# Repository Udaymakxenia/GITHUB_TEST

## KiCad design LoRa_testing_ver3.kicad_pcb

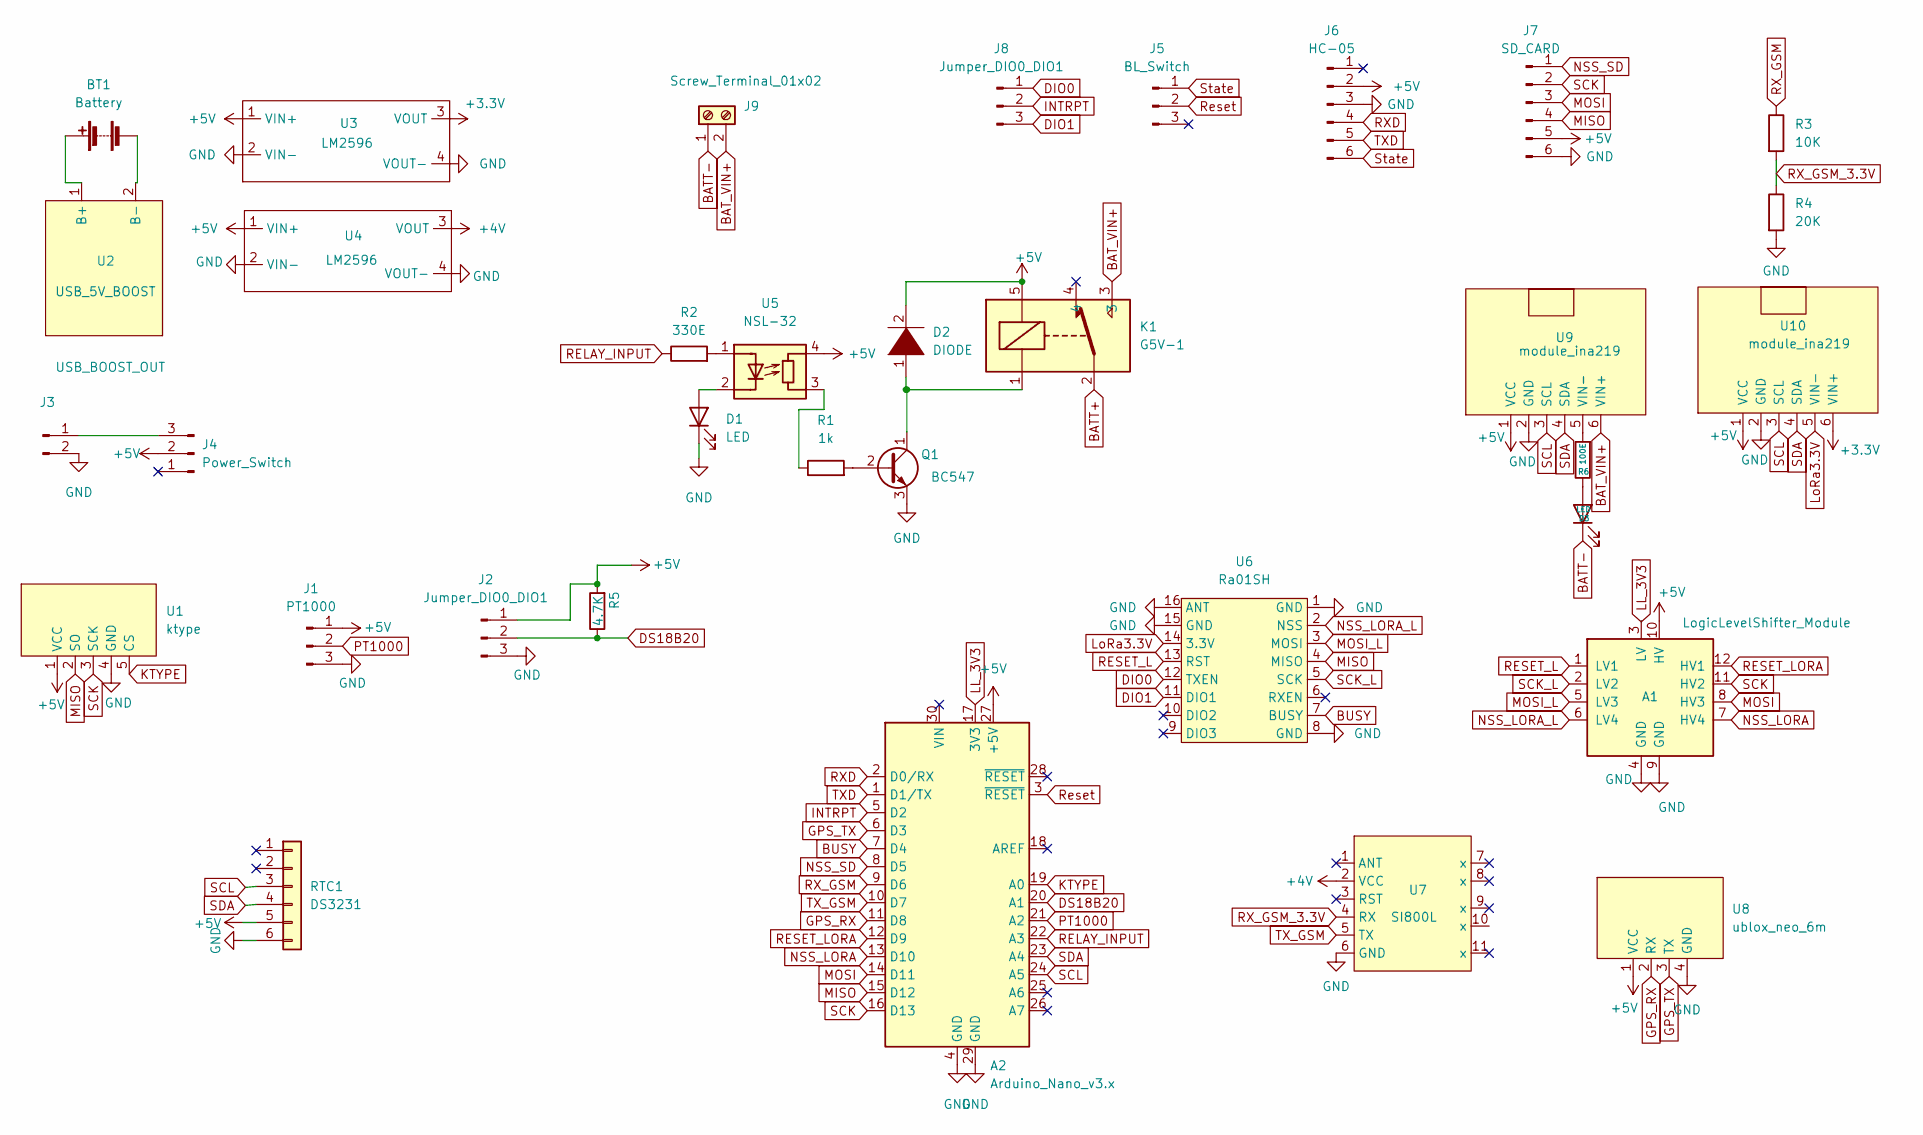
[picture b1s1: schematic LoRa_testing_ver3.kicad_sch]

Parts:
A1: LogicLevelShifter_Module; PinHeader_1x12_P2.54mm_Vertical
A2: Arduino_Nano_v3.x; Arduino_Nano
BT1: Battery; BatteryHolder_MPD_BH-18650-PC2
D1: LED; LED_D3.0mm
D2: DIODE; D_DO-41_SOD81_P3.81mm_Vertical_AnodeUp
D3: LED; LED_D5.0mm
J1: PT1000; PinHeader_1x03_P2.54mm_Vertical
J2, J8: Jumper_DIO0_DIO1; PinHeader_1x03_P2.54mm_Vertical
J3: USB_BOOST_OUT; PinHeader_1x02_P2.54mm_Vertical
J4: Power_Switch; PinHeader_1x03_P2.54mm_Vertical
J5: BL_Switch; PinHeader_1x03_P2.54mm_Vertical
J6: HC-05; PinHeader_1x06_P2.54mm_Vertical
J7: SD_CARD; PinHeader_1x06_P2.54mm_Vertical
J9: Screw_Terminal_01x02; TerminalBlock_Phoenix_MKDS-1,5-2-5.08_1x02_P5.08mm_Horizont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
K1: G5V-1; Relay_SPDT_SANYOU_SRD_Series_Form_C
Q1: BC547; TO-92_Inline
R1: 1k; R_Axial_DIN0207_L6.3mm_D2.5mm_P7.62mm_Horizontal
R2: 330E; R_Axial_DIN0411_L9.9mm_D3.6mm_P7.62mm_Vertical
R3: 10K; R_Axial_DIN0207_L6.3mm_D2.5mm_P7.62mm_Horizontal
R4: 20K; R_Axial_DIN0207_L6.3mm_D2.5mm_P7.62mm_Horizontal
R5: 4.7K; R_Axial_DIN0207_L6.3mm_D2.5mm_P7.62mm_Horizontal
R6: 100E; R_Axial_DIN0207_L6.3mm_D2.5mm_P10.16mm_Horizontal
RTC1: DS3231; PinHeader_1x06_P2.54mm_Vertical
U1: ktype; PinHeader_1x05_P2.54mm_Vertical
U2: USB_5V_BOOST; PinHeader_1x06_P2.54mm_Vertical
U3, U4: LM2596
U5: NSL-32; OPTOCOUPLER
U6: Ra01SH; LoRa Ra01sh
U7: SI800L; GSM
U8: ublox_neo_6m; PinHeader_1x04_P2.54mm_Vertical
U9, U10: module_ina219

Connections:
+3.3V: U3.3 (VOUT), U10.6 (VIN+)
+4V: U4.3 (VOUT), U7.2 (VCC)
+5V: A1.10 (HV), A2.27 (+5V), D2.2 (A), J1.1, J2.1, J4.2, J6.2, J7.5, K1.5, R5.2, RTC1.5, U1.1 (VCC), U3.1 (VIN+), U4.1 (VIN+), U5.4 (R), U8.1 (VCC), U9.1 (VCC), U10.1 (VCC)
BATT+: K1.2, K1.6
BATT-: D3.1 (K), J9.1
BAT_VIN+: J9.2, K1.3, U9.6 (VIN+)
BUSY: A2.7 (D4), U6.7 (BUSY)
DIO0: J8.1, U6.12 (TXEN)
DIO1: J8.3, U6.11 (DIO1)
DS18B20: A2.20 (A1), J2.2, R5.1
GND: A1.4 (GND), A1.9 (GND), A2.4 (GND), A2.29 (GND), D1.1 (K), J1.3, J2.3, J3.2, J6.3, J7.6, Q1.3 (E), R4.2, RTC1.6, U1.4 (GND), U3.2 (VIN-), U3.4 (VOUT-), U4.2 (VIN-), U4.4 (VOUT-), U6.1 (GND), U6.8 (GND), U6.15 (GND), U6.16 (ANT), U7.6 (GND), U8.4 (GND), U9.2 (GND), U10.2 (GND)
GPS_RX: A2.11 (D8), U8.2 (RX)
GPS_TX: A2.6 (D3), U8.3 (TX)
INTRPT: A2.5 (D2), J8.2
KTYPE: A2.19 (A0), U1.5 (CS)
LL_3V3: A1.3 (LV), A2.17 (3V3)
LoRa3.3V: U6.14 (3.3V), U10.5 (VIN-)
MISO: A2.15 (D12), J7.4, U1.2 (SO), U6.4 (MISO)
MOSI: A1.8 (HV3), A2.14 (D11), J7.3
MOSI_L: A1.5 (LV3), U6.3 (MOSI)
NSS_LORA: A1.7 (HV4), A2.13 (D10)
NSS_LORA_L: A1.6 (LV4), U6.2 (NSS)
NSS_SD: A2.8 (D5), J7.1
unnamed: BT1.1 (+), U2.1 (B+)
unnamed: BT1.2 (-), U2.2 (B-)
unnamed: D1.2 (A), U5.2 (K)
unnamed: D2.1 (K), K1.1, Q1.1 (C)
unnamed: D3.2 (A), R6.1
unnamed: J3.1, J4.3
unnamed: Q1.2 (B), R1.2
unnamed: R1.1, U5.3 (R)
unnamed: R2.2, U5.1 (A)
unnamed: R6.2, U9.5 (VIN-)
PT1000: A2.21 (A2), J1.2
RELAY_INPUT: A2.22 (A3), R2.1
RESET_L: A1.1 (LV1), U6.13 (RST)
RESET_LORA: A1.12 (HV1), A2.12 (D9)
RXD: A2.2 (D0/RX), J6.4
RX_GSM: A2.9 (D6), R3.1
RX_GSM_3.3V: R3.2, R4.1, U7.4 (RX)
Reset: A2.3 (~RESET), J5.2
SCK: A1.11 (HV2), A2.16 (D13), J7.2, U1.3 (SCK)
SCK_L: A1.2 (LV2), U6.5 (SCK)
SCL: A2.24 (A5), RTC1.3, U9.3 (SCL), U10.3 (SCL)
SDA: A2.23 (A4), RTC1.4, U9.4 (SDA), U10.4 (SDA)
State: J5.1, J6.6
TXD: A2.1 (D1/TX), J6.5
TX_GSM: A2.10 (D7), U7.5 (TX)

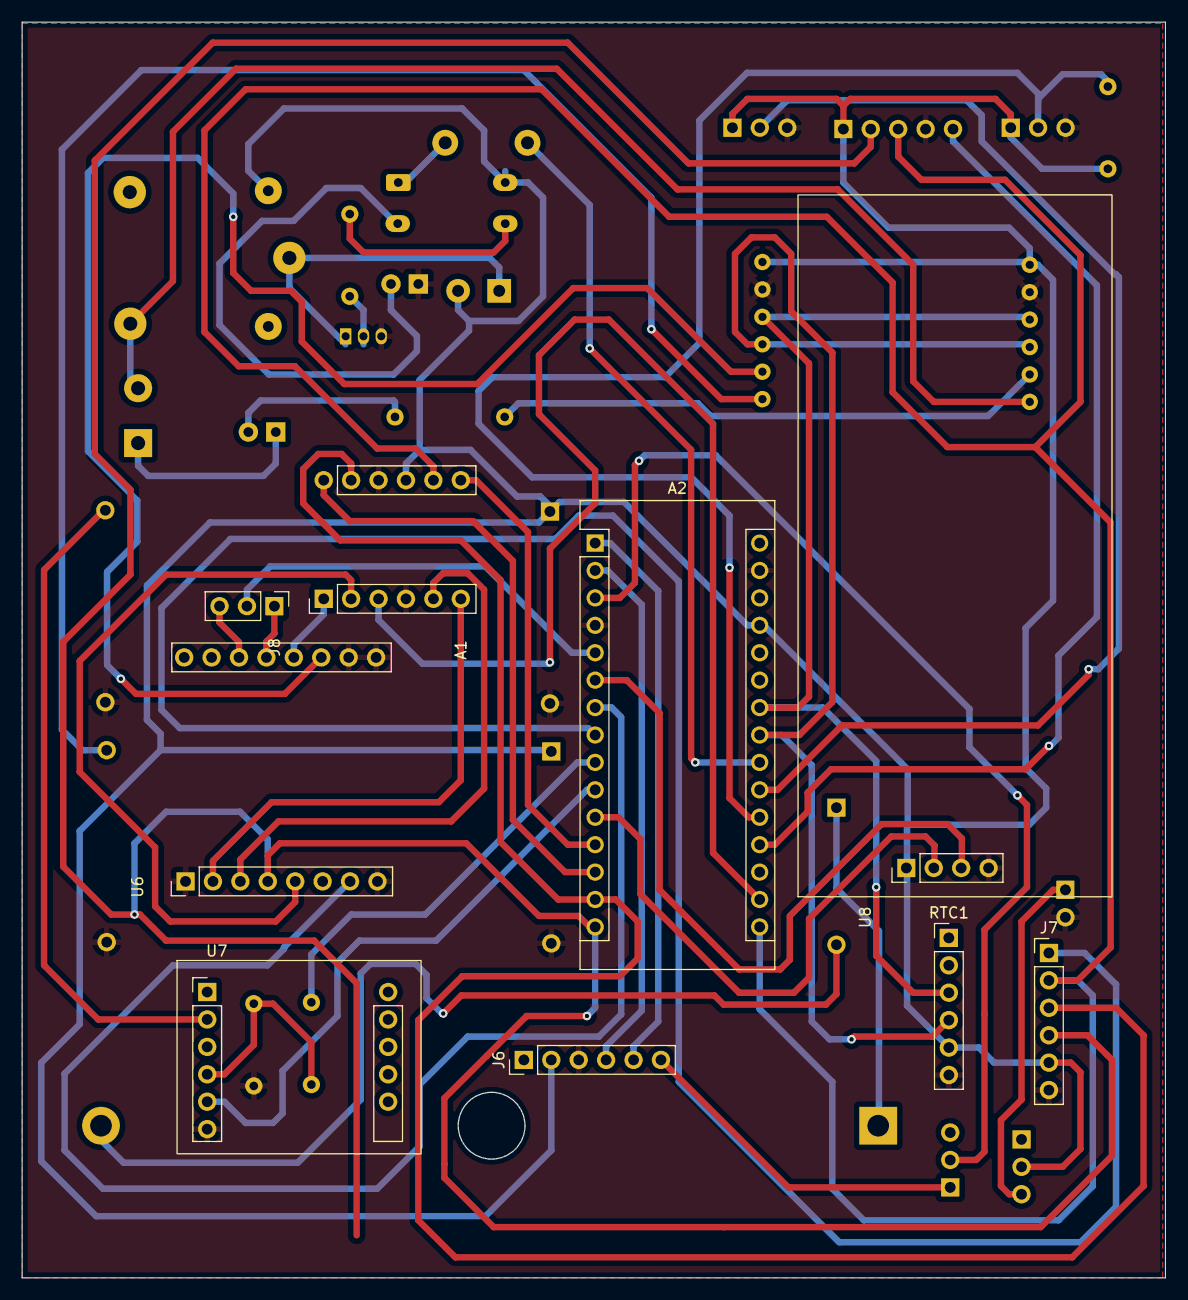
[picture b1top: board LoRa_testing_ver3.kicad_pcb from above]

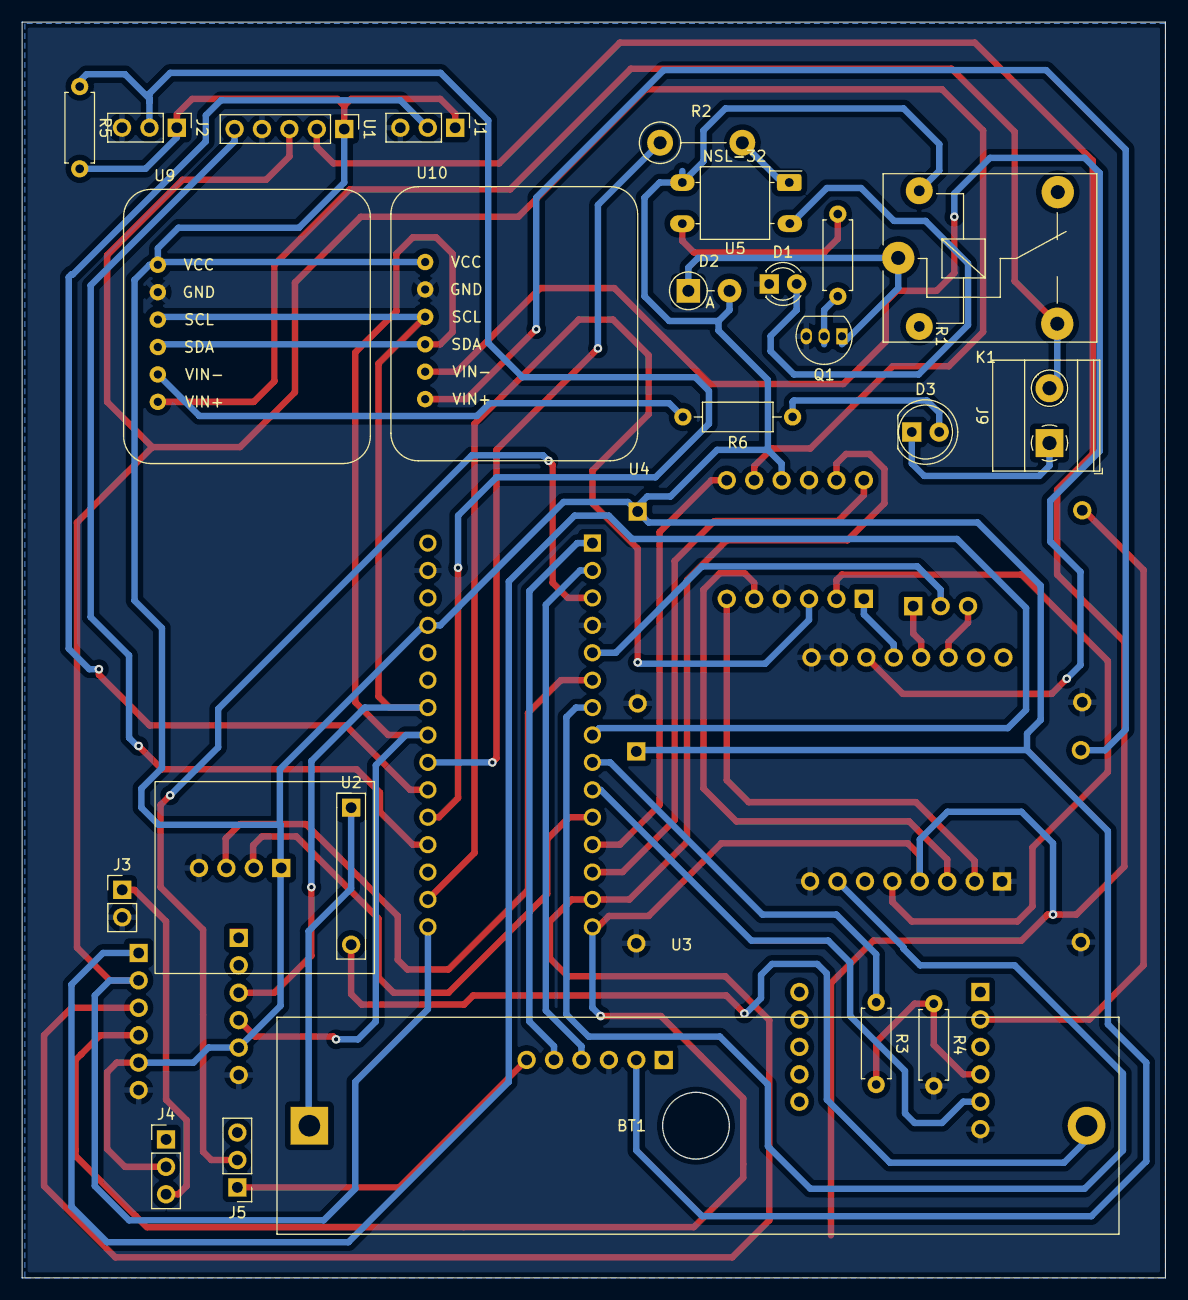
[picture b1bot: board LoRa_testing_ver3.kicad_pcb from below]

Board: 2 copper layers, 105.9 x 116.3 mm, 34 parts (25 on the bottom side), 47 nets.

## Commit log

2022-11-12 Added main Kicad Files
